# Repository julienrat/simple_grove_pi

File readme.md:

PCB Simple Grove PI
======================================

PCB permettant de connecter des modules groves au rapsberry PI,

Les fichiers de production ainsi que la BOM sont disposibles dans le répertoire prod_seedstudio et sont destinés à etre utilisés avec les services seeedstudio prototyping
http://www.seeedstudio.com/service/index.php?r=site/pcbService&type=pcba

Les fichiers sources sont compatibles EAGLE avec la librairie Open Parts Library  (http://www.seeedstudio.com/wiki/Open_parts_library)
Licence GNU GPL

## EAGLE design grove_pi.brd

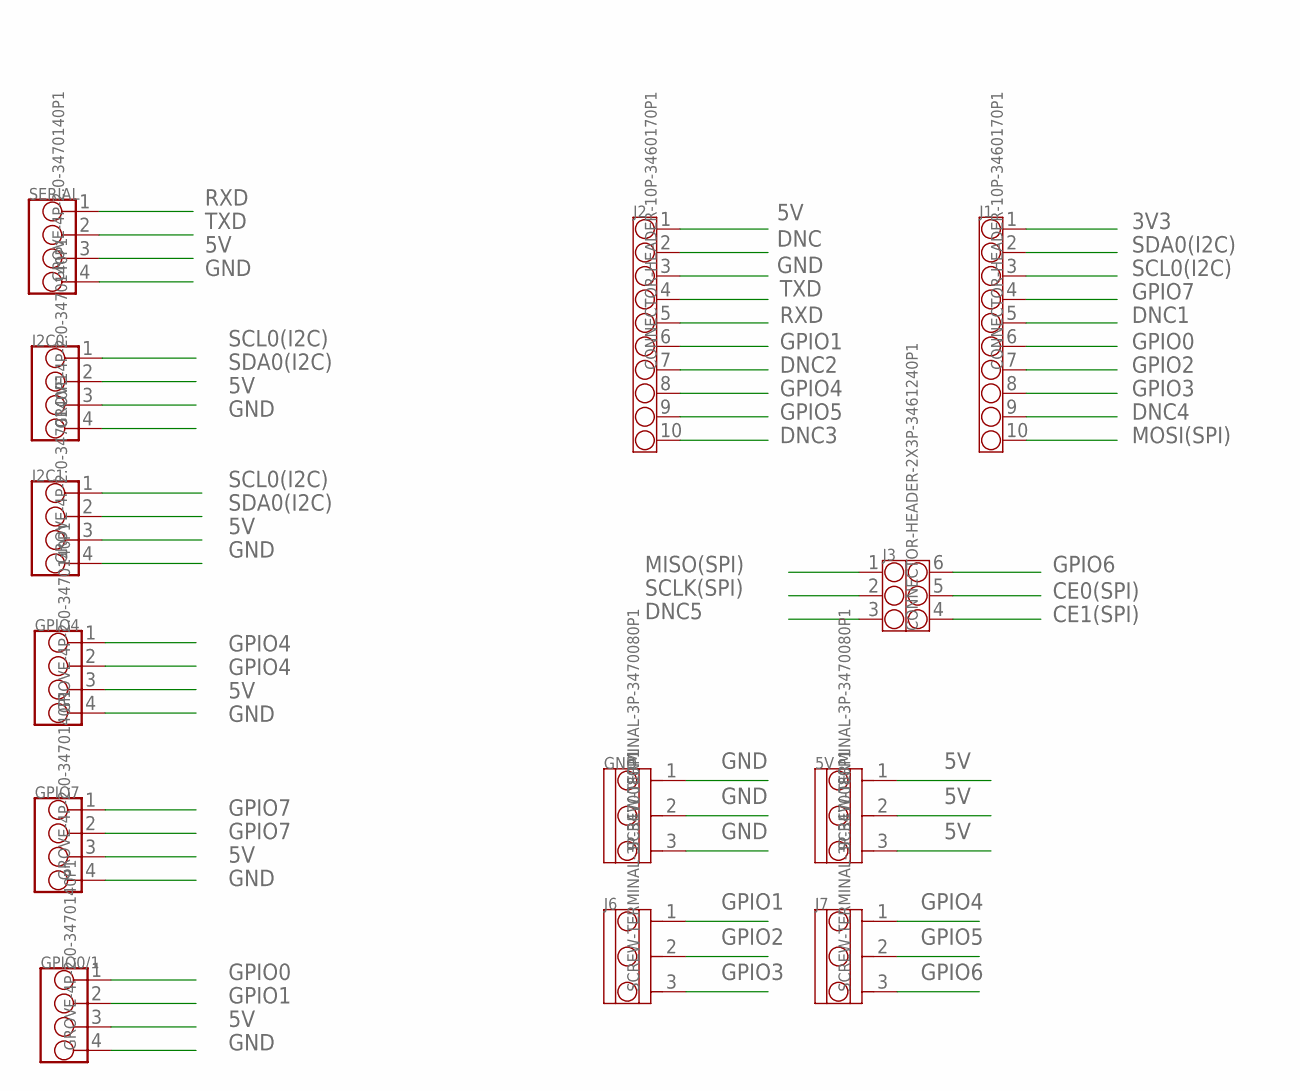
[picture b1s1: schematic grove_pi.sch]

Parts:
5V: SCREW-TERMINAL-3P-3470080P1; 3P-5.0
GND: SCREW-TERMINAL-3P-3470080P1; 3P-5.0
GPIO0/1, GPIO4, GPIO7: GROVE-4P-2.0-3470140P1; 4P-2.0-90D
I2C0, I2C1: GROVE-4P-2.0-3470140P1; 4P-2.0-90D
J1, J2: CONNECTOR-HEADER-10P-3460170P1; 1X10P-2.54-8.5-YELLOW-FEMALE
J3: CONNECTOR-HEADER-2X3P-3461240P1; 2X3P-2.54-8.5+1.5-12.3-BLUE-FEMALE
J6, J7: SCREW-TERMINAL-3P-3470080P1; 3P-5.0
SERIAL: GROVE-4P-2.0-3470140P1; 4P-2.0-90D

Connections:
3V3: J1.1
5V: 5V.1, 5V.2, 5V.3, GPIO0/1.3, GPIO4.3, GPIO7.3, I2C0.3, I2C1.3, J2.1, SERIAL.3
CE0(SPI): J3.5
CE1(SPI): J3.4
DNC: J2.2
DNC1: J1.5
DNC2: J2.7
DNC3: J2.10
DNC4: J1.9
DNC5: J3.3
GND: GND.1, GND.2, GND.3, GPIO0/1.4, GPIO4.4, GPIO7.4, I2C0.4, I2C1.4, J2.3, SERIAL.4
GPIO0: GPIO0/1.1, J1.6
GPIO1: GPIO0/1.2, J2.6, J6.1
GPIO2: J1.7, J6.2
GPIO3: J1.8, J6.3
GPIO4: GPIO4.1, GPIO4.2, J2.8, J7.1
GPIO5: J2.9, J7.2
GPIO6: J3.6, J7.3
GPIO7: GPIO7.1, GPIO7.2, J1.4
MISO(SPI): J3.1
MOSI(SPI): J1.10
RXD: J2.5, SERIAL.1
SCL0(I2C): I2C0.1, I2C1.1, J1.3
SCLK(SPI): J3.2
SDA0(I2C): I2C0.2, I2C1.2, J1.2
TXD: J2.4, SERIAL.2

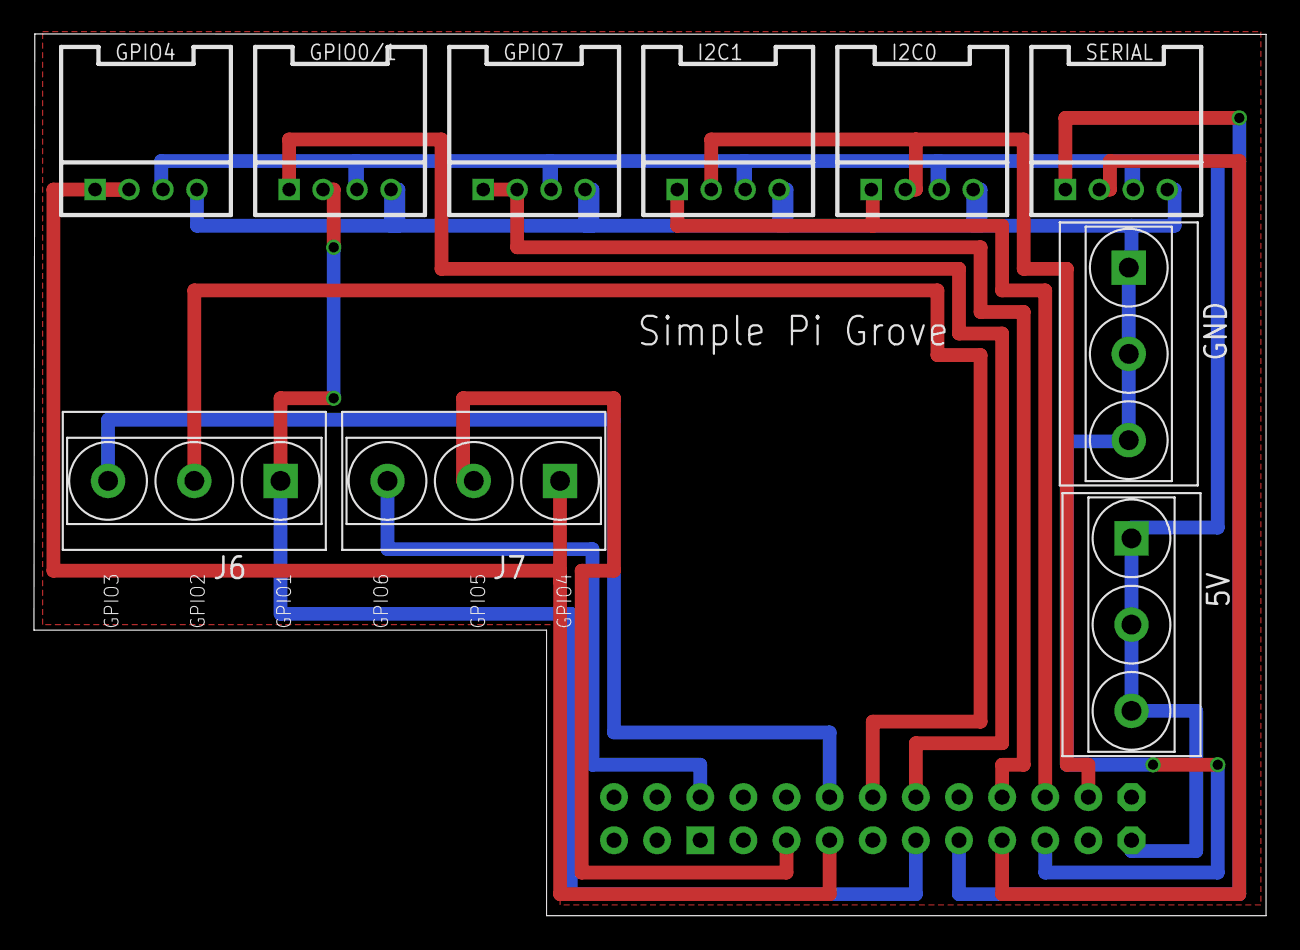
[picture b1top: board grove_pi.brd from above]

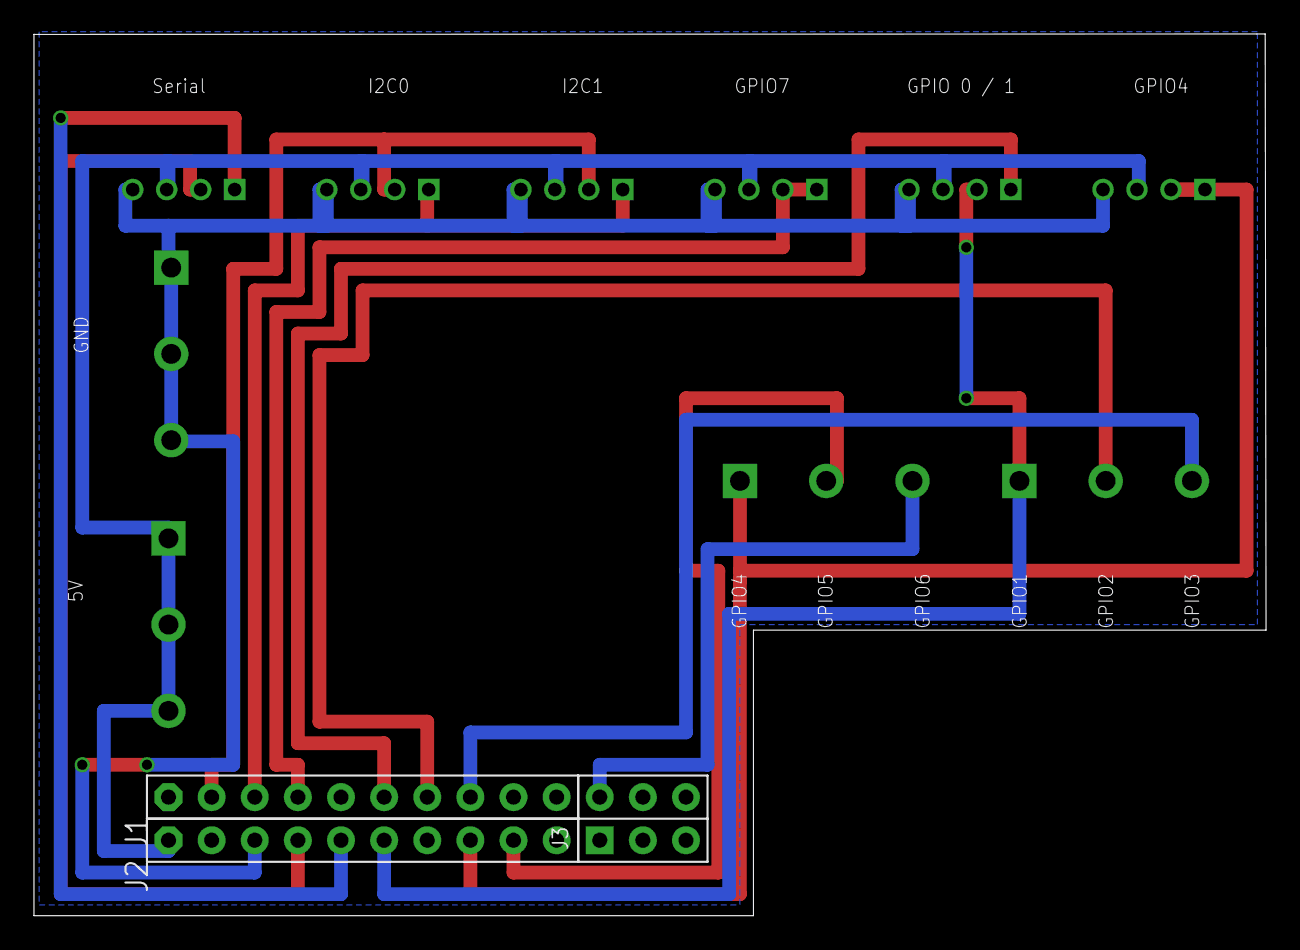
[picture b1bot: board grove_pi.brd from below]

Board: 4 copper layers, 72.6 x 51.9 mm, 13 parts (3 on the bottom side), 14 nets.

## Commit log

2013-12-11 ajout du PCB
2013-12-11 ajout du readme
